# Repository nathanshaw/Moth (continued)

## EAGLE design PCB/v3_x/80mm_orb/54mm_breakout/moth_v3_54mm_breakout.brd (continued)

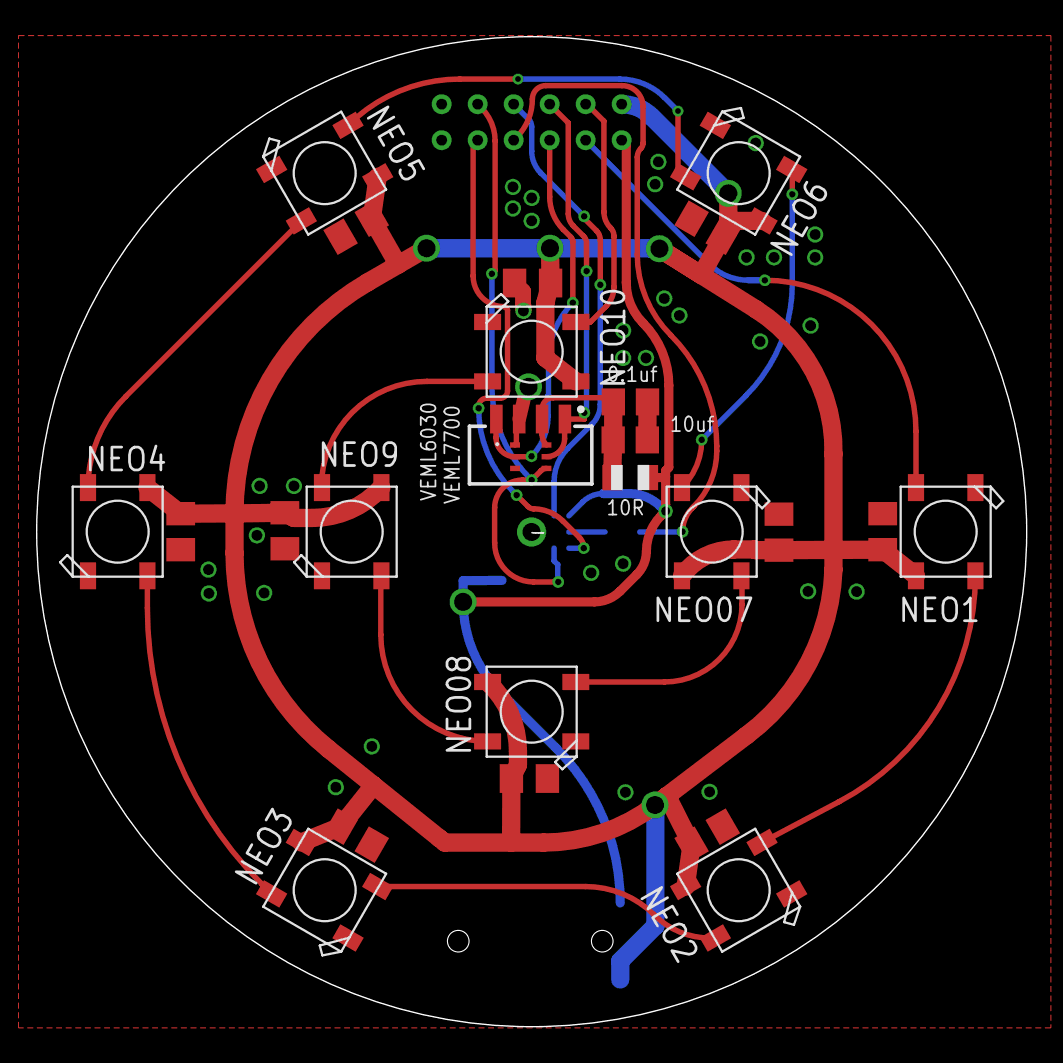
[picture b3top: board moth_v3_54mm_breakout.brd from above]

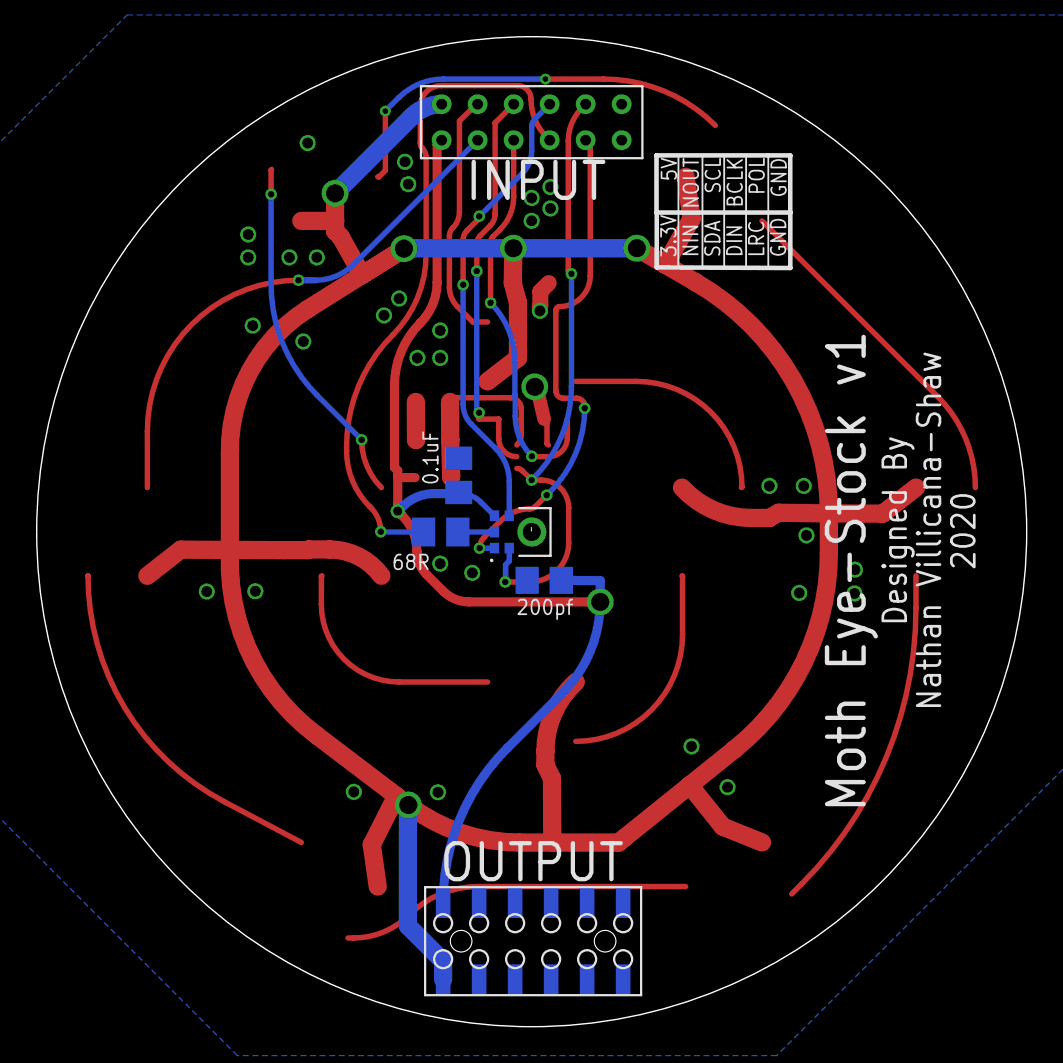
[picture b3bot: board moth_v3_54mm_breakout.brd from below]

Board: 2 copper layers, 55.0 x 55.0 mm, 31 parts (6 on the bottom side), 22 nets.

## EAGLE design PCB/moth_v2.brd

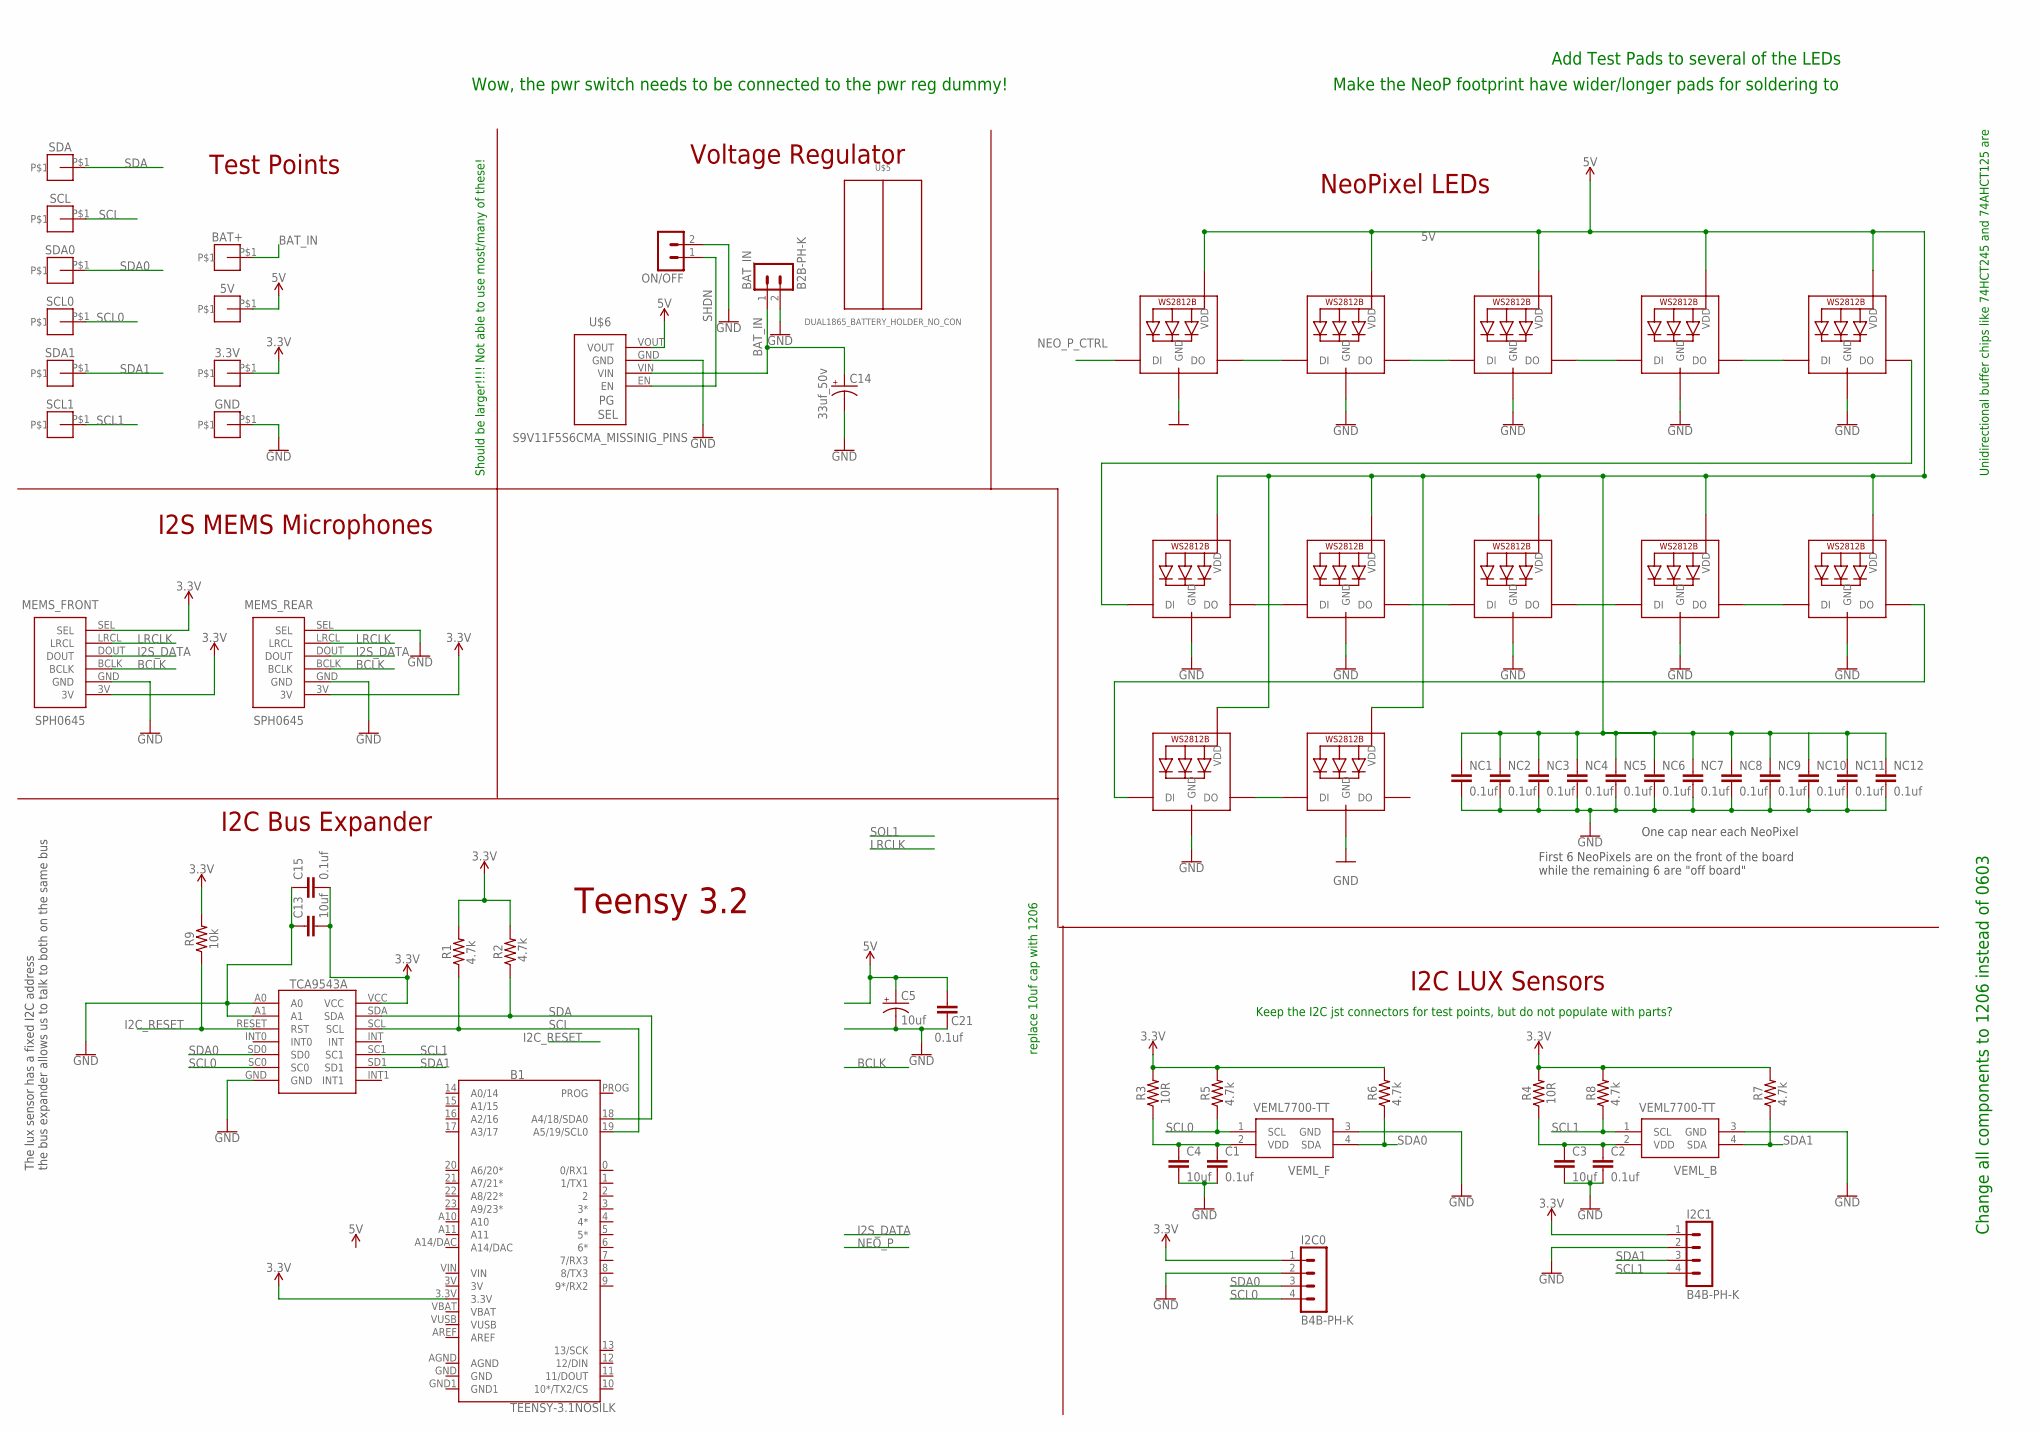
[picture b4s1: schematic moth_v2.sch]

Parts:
3.3V, 5V: TEST_POINT_LARGE
B1: TEENSY-3.1NOSILK; TEENSY-3.1_NOSILK
BAT+: TEST_POINT_LARGE
BAT_IN: B2B-PH-K
C1, C2, C15, C21: 0.1uf; 0603
C3, C4, C13: 10uf; 0603
C5: 10uf; E2,5-6
C14: 33uf_50v; E2-5
GND: TEST_POINT_LARGE
I2C0, I2C1: B4B-PH-K
MEMS_FRONT: SPH0645
MEMS_REAR: SPH0645
NC1, NC2, NC3, NC4, NC5, NC6, NC7, NC8, NC9, NC10, NC11, NC12: 0.1uf; 0603
NEO_01, NEO_02, NEO_03, NEO_04, NEO_05, NEO_06, NEO_07, NEO_08, NEO_09, NEO_10, NEO_11, NEO_12: WS2812B_5050N; WS2812B-NARROW
ON/OFF: B2B-PH-K
R1, R2, R5, R6, R7, R8: 4.7k; 0207/10
R3, R4: 10R; 0603
R9: 10k; 0207/10
SCL, SCL0, SCL1: TEST_POINT_LARGE
SDA, SDA0, SDA1: TEST_POINT_LARGE
U$1: TCA9543A; SO14
U$5: DUAL1865_BATTERY_HOLDER_NO_CON; DUAL_18650_BAT_HOLDER_NO_CON
U$6: S9V11F5S6CMA_MISSINIG_PINS; S9V11F3S5CMA_MISSING_PINS
VEML_B: VEML7700-TT; VEML7700
VEML_F: VEML7700-TT; VEML7700

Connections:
3.3V: 3.3V.P$1, B1.3.3V, C13.2, C15.2, I2C0.1, I2C1.1, MEMS_FRONT.3V, MEMS_FRONT.SEL, MEMS_REAR.3V, R1.2, R2.2, R3.2, R4.2, R5.2, R6.2, R7.2, R8.2, R9.2, U$1.VCC
3V: B1.3V
5V: 5V.P$1, C5.+, C21.2, NC1.1, NC2.1, NC3.1, NC4.1, NC5.1, NC6.1, NC7.1, NC8.1, NC9.1, NC10.1, NC11.1, NC12.1, NEO_01.1-VDD (VDD), NEO_02.1-VDD (VDD), NEO_03.1-VDD (VDD), NEO_04.1-VDD (VDD), NEO_05.1-VDD (VDD), NEO_06.1-VDD (VDD), NEO_07.1-VDD (VDD), NEO_08.1-VDD (VDD), NEO_09.1-VDD (VDD), NEO_10.1-VDD (VDD), NEO_11.1-VDD (VDD), NEO_12.1-VDD (VDD), U$6.VOUT
AGND: B1.AGND
BAT_IN: BAT+.P$1, BAT_IN.1, C14.+, U$6.VIN
BCLK: MEMS_FRONT.BCLK, MEMS_REAR.BCLK
GND: B1.GND, BAT_IN.2, C1.2, C2.2, C3.2, C4.2, C5.-, C13.1, C14.-, C15.1, C21.1, GND.P$1, I2C0.2, I2C1.2, MEMS_FRONT.GND, MEMS_REAR.GND, MEMS_REAR.SEL, NC1.2, NC2.2, NC3.2, NC4.2, NC5.2, NC6.2, NC7.2, NC8.2, NC9.2, NC10.2, NC11.2, NC12.2, NEO_01.3-GND (GND), NEO_02.3-GND (GND), NEO_03.3-GND (GND), NEO_04.3-GND (GND), NEO_05.3-GND (GND), NEO_06.3-GND (GND), NEO_07.3-GND (GND), NEO_08.3-GND (GND), NEO_09.3-GND (GND), NEO_10.3-GND (GND), NEO_11.3-GND (GND), NEO_12.3-GND (GND), ON/OFF.2, U$1.A0, U$1.A1, U$1.GND, U$6.GND, VEML_B.3 (GND), VEML_F.3 (GND)
GND1: B1.GND1
I2C_RESET: R9.1, U$1.RESET (RST)
I2S_DATA: MEMS_FRONT.DOUT, MEMS_REAR.DOUT
LRCLK: MEMS_FRONT.LRCL, MEMS_REAR.LRCL
unnamed: C1.1, C4.1, R3.1, VEML_F.2 (VDD)
unnamed: C2.1, C3.1, R4.1, VEML_B.2 (VDD)
unnamed: NEO_02.2-DOUT (DO), NEO_03.4-DIN (DI)
unnamed: NEO_05.2-DOUT (DO), NEO_06.4-DIN (DI)
unnamed: NEO_11.2-DOUT (DO), NEO_12.4-DIN (DI)
unnamed: NEO_04.2-DOUT (DO), NEO_05.4-DIN (DI)
unnamed: NEO_03.2-DOUT (DO), NEO_04.4-DIN (DI)
unnamed: NEO_07.2-DOUT (DO), NEO_08.4-DIN (DI)
unnamed: NEO_08.2-DOUT (DO), NEO_09.4-DIN (DI)
unnamed: NEO_09.2-DOUT (DO), NEO_10.4-DIN (DI)
unnamed: NEO_10.2-DOUT (DO), NEO_11.4-DIN (DI)
unnamed: NEO_06.2-DOUT (DO), NEO_07.4-DIN (DI)
NEO_P1: NEO_01.2-DOUT (DO), NEO_02.4-DIN (DI)
NEO_P_CTRL: NEO_01.4-DIN (DI)
SCL: B1.19 (A5/19/SCL0), R1.1, SCL.P$1, U$1.SCL
SCL0: I2C0.4, R5.1, SCL0.P$1, U$1.SC0, VEML_F.1 (SCL)
SCL1: I2C1.4, R8.1, SCL1.P$1, U$1.SC1, VEML_B.1 (SCL)
SDA: B1.18 (A4/18/SDA0), R2.1, SDA.P$1, U$1.SDA
SDA0: I2C0.3, R6.1, SDA0.P$1, U$1.SD0, VEML_F.4 (SDA)
SDA1: I2C1.3, R7.1, SDA1.P$1, U$1.SD1, VEML_B.4 (SDA)
SHDN: ON/OFF.1, U$6.EN
VBAT: B1.VBAT
VIN: B1.VIN
VUSB: B1.VUSB

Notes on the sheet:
I2S MEMS Microphones
Voltage Regulator
Teensy 3.2
I2C LUX Sensors
I2C Bus Expander
NeoPixel LEDs
10k
4.7k
One cap near each NeoPixel
First 6 NeoPixels are on the front of the board while the remaining 6 are "off board"
The lux sensor has a fixed I2C address the bus expander allows us to talk to both on the same bus
Test Points
Unidirectional buffer chips like 74HCT245 and 74AHCT125 are
Should be larger!!!! Not able to use most/many of these!
Change all components to 1206 instead of 0603
Make the NeoP footprint have wider/longer pads for soldering to
Add Test Pads to several of the LEDs
Wow, the pwr switch needs to be connected to the pwr reg dummy!
replace 10uf cap with 1206
Keep the I2C jst connectors for test points, but do not populate with parts?

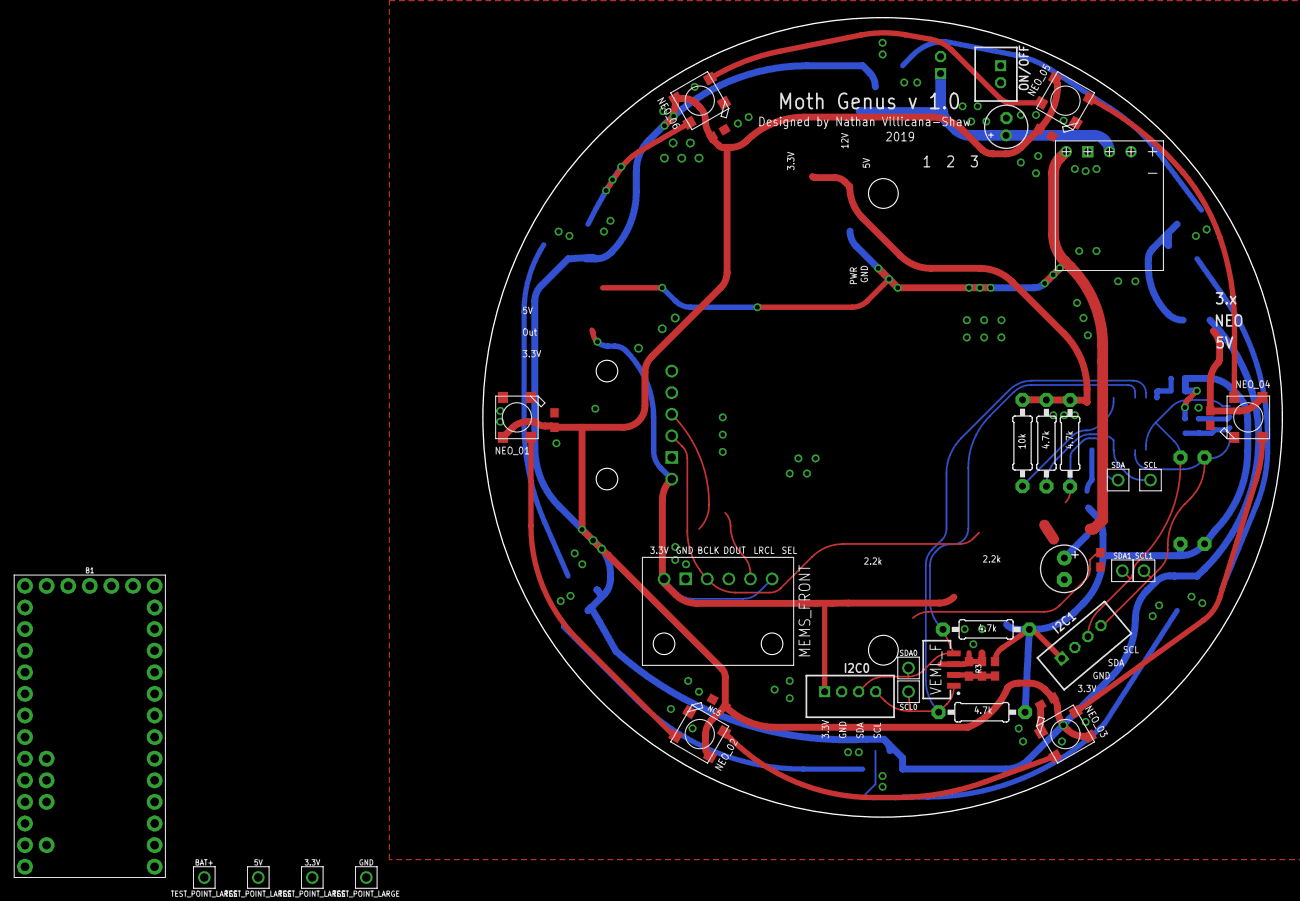
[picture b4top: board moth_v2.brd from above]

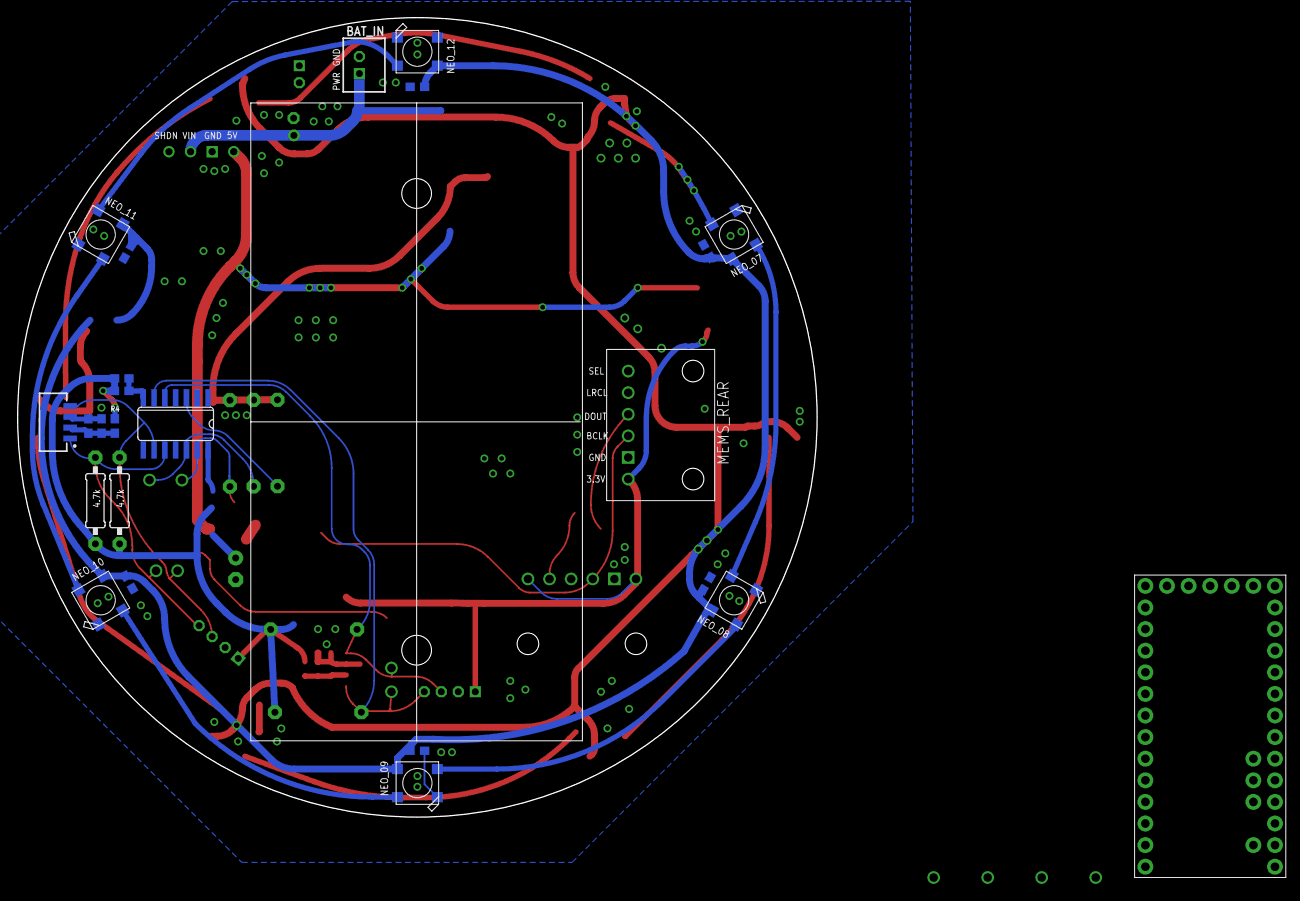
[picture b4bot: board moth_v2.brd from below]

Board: 2 copper layers, 94.0 x 94.0 mm, 64 parts (24 on the bottom side), 28 nets.

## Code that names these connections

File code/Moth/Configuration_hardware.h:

#ifndef __CONFIGURATION_ADV_H__
#define __CONFIGURATION_ADV_H__
// contains all the hardware specific variables
#define HARDWARE_NAME "Moth"
#include "PrintUtils.h"
#include "Macros.h"

#define HV_MAJOR                  2
#define HV_MINOR                  1
// FIRMWARE MODE should be set to  CICADA_MODE, PITCH_MODE, or TEST_MODE
// depending on what functionality you want
#define FIRMWARE_MODE             PITCH_MODE

// Currently there are four options for the enclosure : 
//         GROUND_ENCLOSURE 
//         ORB_ENCLOSURE_WITH_HOLE
//         ORB_ENCLOSURE_WITHOUT_HOLE
//         NO_ENCLOSURE
// different enclosures result in a different amount of attenuation from environmental sounds.
// the orb enclosure forms the base-line for this, it is thin and dones attneuate sounds but not nearly as much as the ground enclosure.
uint8_t ENCLOSURE_TYPE =          ORB_ENCLOSURE_WITHOUT_HOLE;

#if ENCLOSURE_TYPE == ORB_ENCLOSURE_WITH_HOLE
double ENC_ATTENUATION_FACTOR =        1.0;
#elif ENCLOSURE_TYPE == ORB_ENCLOSURE_WITHOUT_HOLE
double ENC_ATTENUATION_FACTOR =        2.0;
#elif ENCLOSURE_TYPE == GROUND_ENCLOSURE
double ENC_ATTENUATION_FACTOR =        3.0;
#elif ENCLOSURE_TYPE == NO_ENCLOSURE
double ENC_ATTENUATION_FACTOR =        0.75;
#endif

// different microcontrollers which can be used for the system
#define TEENSY30                  0
#define TEENSY32                  1
#define TEENSY35                  2
#define TEENSY36                  3
#define TEENSY40                  4

#define MICROCONTROLLER           TEENSY32

#if HV_MAJOR > 1
#define NUM_LUX_SENSORS           2
#endif

// todo add logic to change these if needed...
#if (HV_MAJOR == 3)
#define NUM_LED                   40
#endif

#if (HV_MAJOR == 2 && HV_MINOR == 0)
#define NUM_LED                   12
#endif

#if (HV_MAJOR == 2 && HV_MINOR == 1)
#define NUM_LED                   10
#endif 

#define FRONT_MICROPHONE_INSTALLED      true
#define REAR_MICROPHONE_INSTALLED       true

////////////// TCA Bus Expanders     /////
// I2C_MULTI should be 0 if no TCA I2C bus expander is present on the PCB
// I2C MULTI should be 1 if a TCA I2C bus expander is present
#if HV_MAJOR < 3
#define I2C_MULTI                 1
// the number of active channels on the TCA (can in theory support 8 sensors, etc.)
#define TCA_CHANNELS              2
#else
#define I2C_MULTI                 0
#define TCA_CHANNELS              0 
#endif

//////////// MICROCONTROLLER PIN OUTS ////
#define LED_PIN                   5

//////////// User Controls /////////////////
#if HV_MAJOR < 3
#define NUM_JUMPERS               6
#define JMP1_PIN                  12
#define JMP2_PIN                  11
#define JMP3_PIN                  14
#define JMP4_PIN                  15
#define JMP5_PIN                  16
#define JMP6_PIN                  17
#define NUM_POTS                  0
int jmp_pins[NUM_JUMPERS] = {JMP1_PIN, JMP2_PIN, JMP3_PIN, JMP4_PIN, JMP5_PIN,
                             JMP6_PIN};

#elif HV_MAJOR == 3
#define NUM_JUMPERS               10

#define JMP1_PIN                  14
#define JMP2_PIN                  12
#define JMP3_PIN                  11
#define JMP4_PIN                  10
#define JMP5_PIN                  8
#define JMP6_PIN                  7
#define JMP7_PIN                  6
#define JMP8_PIN                  4
#define JMP9_PIN                  3
#define JMP10_PIN                 2

int jmp_pins[NUM_JUMPERS] = {JMP1_PIN, JMP2_PIN, JMP3_PIN, JMP4_PIN, JMP5_PIN,
                             JMP6_PIN, JMP7_PIN, JMP8_PIN, JMP9_PIN, JMP10_PIN};

#define NUM_POTS                  4
#define POT1_PIN                  22
#define POT2_PIN                  21
#define POT3_PIN                  20
#define POT4_PIN                  17

int pot_pins[NUM_POTS] = {POT1_PIN, POT2_PIN, POT3_PIN, POT4_PIN};
uint16_t pot_vals[NUM_POTS] = {0, 0, 0, 0};

#endif

// TODO - need  to move some of this to the EEPROM storage, and add a flag in the standard configuratui file to  either read that information or to write it
// how long does the microphone test routine last for in the feature collector testMicrophone() function
#define MICROPHONE_TEST_DURATION  1500
#define LUX_TEST_DURATION         1000

////////////////////////////////////////////////////////////////////////////
///////////////////////// Jumper Settings //////////////////////////////////
////////////////////////////////////////////////////////////////////////////
// turn on/off reading jumpers in setup (if off take the default "true" values for jumper bools
#define JUMPERS_POPULATED               1

#endif // __HARDWARE_CONFIGURATION_H__

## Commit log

2019-08-21 init commit
2019-09-05 added back the test files
2019-09-05 fixed bug in veml test
2019-09-05 fixed typo in neop test
2019-09-05 working out the tca code
2019-09-09 moved some things around
2019-09-09 made sure that the file moves is tracked properly
2019-09-09 added lux and neop test and the neop test into the repo
2019-09-10 added a teensy firmware file for using the audio library, as well as a .gitignore with DS_Store files added
2019-09-11 added some more neop tests, tested the analysis_prototyping and updated for pi-town
2019-09-12 started putting all the pieces together in the main.py file, moved the neopixel tests to their own folder
2019-09-12 got the neop's changing brightness according to lux
2019-09-12 removing fluff from the chuck code, further updates to OSC communication in the python code
2019-09-12 cleaned up the chuck code
2019-09-12 working through the neopixel issue when running chuck
2019-09-12 created a simple rms osc sender chuck program to test things
2019-09-17 got some more test scripts
2019-10-05 worked out some tests for possibly using the Teensy instead of the Pi for the project
2019-10-08 got a working rough version of the teensy_tests for moth working correctly
2019-10-09 added the cicada wav file, the PCB EAGLE files and a few teensy tests for the repo
2019-10-09 got a working version of the VEML sensors working through the TCA9543A
2019-10-10 new but untested auto_gain control also minor updates to the v2 PCB
2019-10-15 finished the v2 PCB
2019-10-15 got rid of old files
2019-10-18 got a working POC version of the code in which the gain auto adjust and the veml lux readings are functioning
2019-10-28 added the final v2.1 of the PCB, updated the firmware to a place where it can handle stereo audio more or less and the use of both lux sensors
2019-10-28 reworked the folder structure for the repo
2019-11-23 started a v3 of the code after working hard on a refactoring to move some parts out into libraries which can be used in other projects
2019-11-23 added a pdf of the v1 moth pcb
2019-11-25 creaded v3 of the code which is modular with the goal of being used on lyre and other bots
2019-11-26 code at v 3.0.3
2019-11-27 got a working version of the pitch mode added, now I am going to try and add its functionality to the main Moth code
2019-11-27 integrated the two modes into one program, dubbed it 3.1.0 =)
2019-11-27 got a rough version of the hsb mapping working
2019-12-02 working more on the refactor, things are broken at the momemt, working on rebuilding the datalogging library better
2019-12-02 working version of the code, the datalogging is not implemented, but the original code works with parts of the datalogging code added, or at least in the cicada mode
2019-12-03 got another working version of the code with a little more o f the datalog working
2019-12-04 check point where both the setup config logging and the continious datalogging both work
2019-12-04 tested with multiple over-time and once-off logs, everything looks good
2019-12-05 moved software to v 3.1.2, seems to be mostly working like before in cicadaMode
2019-12-05 got 3.1.2 working wellish, got rid of the configuration_adv file, made the current configuration file look much nicer and have better organisation
2019-12-05 fixed the clicks so they work now, the cicadaMode is more or less back to normal, updated the software version to 3.2.0
2019-12-05 removed extra print statement
2019-12-05 got the datalogging working even better, fixed a bug or two, made the print out better, etc, moving the program version up to 3.2.1
2019-12-06 got the auto-gain more or less working now as it was before =)
2019-12-07 everything is broken, moved changes to new branch
2019-12-07 still crap
2019-12-07 trash
2019-12-08 cicada mode working again, haha, pitch is still not so hunky
2019-12-10 fixed some bugs with how static logs are handled, current configuration is for the battery tests
2019-12-10 got both a rough pitch and a rough cicada mode working on the same code, YAY
2019-12-12 working a little more on the refactor
2019-12-13 added datalogging for RGB average avlues, added tracking of RGB average vals to NeoManager, cleaned up the neomanager file a bit
2019-12-13 updated the template file for the creation of new modes, and started with the creation of the new test mode?
2019-12-18 middle of post-field test adjustments
2019-12-18 improved the field test mode to be a little easier to work with
2019-12-18 got stable version of test, pitch and cicada all working, upgraded the version number to 0.0.3
2019-12-18 fixed the non-independent flash option
2019-12-19 added a quicker polling time for the lux sensor when extreme lux conditions are present, tested and confirmed that extreme lux condition logic works when the brightness scalers are independent
2019-12-19 extreme lux working with combined lux as well =)
2020-01-25 first commit, something is wrong, not working as expected
2020-01-28 things are pretty broken haha
2020-02-03 few minor configuration changes
2020-02-05 Added in a low threshold for the song features
2020-02-05 added an enclosure type flag in the firmware, made it so the enclosure type ensures that the rear leds do not go off if the enclosure type is ground_enclosure
2020-02-05 added back a light yellow colour when the Moth is booting up
2020-02-13 moving on to pitch now
2020-02-14 got a basic version of the color to pitch mapping working with the Moth cicada mode
2020-02-17 reworking the feature collectors, started a v3 for the PCB
2020-02-20 moved to v0.0.5
2020-02-22 things seem to be broken
2020-02-22 still broken, commiting so i can move to master
2020-02-23 moving forward, sort of
2020-02-23 got the song more or less fixed, now have an issue with the clicks going crazy
2020-02-23 the brightness is fixed and now it scales locally so it should do a better job dealing with its dynamic range =)
2020-02-24 got a working more responsive, to a degree version of the code working
2020-02-24 moved to version 0.1.0 as the song seems to be working pretty well.
2020-02-27 added in jumpers for minor gain boost and the boot delay timer
2020-02-28 finally got a working version of newsong together
2020-02-29 version 0.2.0
2020-03-01 confirmed that this version of the code works well for cicada song
2020-03-04 getting rid of audio engine and neop manager to then add them as submodules
2020-03-04 dlmanager and luxmanager this time
2020-03-04 everything is added back in as a submodule now
2020-03-13 minor changes
2020-03-13 added constant reading of the onboard jumpers
2020-03-14 got the LuxManager handeling both sensors and reporting a global lux based on the highest value between the sensors
2020-04-23 updated the PCB's with the definitive third version
2020-04-23 moving to updating the code for the third version
2020-04-23 updated AudioEngine and NeoPManager
2020-05-06 updated the breakout board
2020-06-07 working on a version of the code which works well with the new hardware
2020-06-29 got the Cicada code for PCB v2.1 working again, PCB v3 is still not really supported
2020-06-29 pt 2 of last commit adding the LuxManager and NeoPixel Manager changes
2020-06-29 minor changes to the v3 breakout and main board
2020-06-30 got v 0.2.2 up and running, 29 FPS, support for PCB 2.1 and 3.0, support for VEML6030's, slightly improved user commands, fixed issue with LTO compiling causing everything to crash a minute or two in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
2020-07-02 added a first version of center out mapping for PCB v3
2020-07-09 changed PRINT_ to P_, and made it so the first pot controls a master master brightness scaler
2020-07-09 integrated data from DLManager, NeopixelManager, and LuxManageere
2020-07-09 v0.2.2
2020-07-11 v0.0.3 in reaction to thee field expedition, added threshold control for the click thresholds using the 4th pot, switched around some of the user controls, a splt was made in thee functionality of th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
2020-07-26 just after getting PC back, getting ready for general purpose pitch mode testing
2020-07-27 added a few print modes, cleaned up some things, fixed a few typos
2020-07-28 got a working good version of th ecode (more or less) working for v2.1 on pitch mode, just perhaps needs more gain
2020-07-28 added changes to LuxManager and NeopixelManager
2020-07-28 added minor updates to the old legacy tests
2020-07-28 pushed v0.2.5
2020-07-29 v0.2.6
2020-08-01 moved around some test programs
2020-08-02 v0.2.7b
2020-08-10 updated the .gitignore and attributes, tring to change the name of the repo and everything from Moth to Speculator
2020-08-10 added updates to the audio_engine
2020-08-10 moving value tracker to its own class
2020-08-10 added ValueTracker as its own repo
2020-08-10 converted the WeatherManager class into a library
2020-08-10 first working version of WeatherManager addeed
2020-08-10 everything now commits with the addition of the WeatherManager and the reduction of the FFTManager to use floats instead of doubles to try and conserve the amount of dynamic memory
2020-08-10 increased the audio memory from 16 to 24, this can officially be called the commit for v0.3.0, the major issue which needs to be addressed is theunknown memory leakage issue which causes the sketch t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
2020-08-10 isolated the restart issue... it is when the auto-gain manager runs its update...
2020-08-15 getting ready for computer reboot
2020-09-08 moved the luxmanager and neopixelmanager into their own Arduino libraries and out of the repo
2020-09-16 updated ignore and attributes
2020-09-16 updated most images of the layout for the purpose of the thesis
2020-09-21 working on updating code to mirror writing in thesis proper
2020-09-21 updated the AudioEngine and WeatherManager classes
2020-09-22 moved WeatherManager out
2020-09-22 removed the DLManager, added it to global libraries
2020-09-23 moving to a working speculator v1 code
2020-09-23 removed the colorconverter and the audioengine libraries from the main code
2020-09-24 getting everything working with the libraries as they should be working
2020-09-26 moved firmware to v0.4.0 a stable version for pitch (more or less)
2020-09-26 moved the lbs functionality into a file and then moved that file to legacy as the ValueTracker class now plays that role.
2020-09-27 software version 0.4.4
2020-09-27 v0.4.5. --- loading firmware and then installing
